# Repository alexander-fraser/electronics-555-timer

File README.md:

# electronics-555-timer-rev1-0
A single-board solution to the three operating modes of the 555 timer (astable, monostable, and bistable).

Jumpers to bridge for each operating mode:
Astable: 2,4,5;
Monostable: 1,3,4;
Bistable: 1

Issue Log:
- Add +/- markings to silkscreen at power input.
- In bistable mode, the chip resets when JP4 is touched.

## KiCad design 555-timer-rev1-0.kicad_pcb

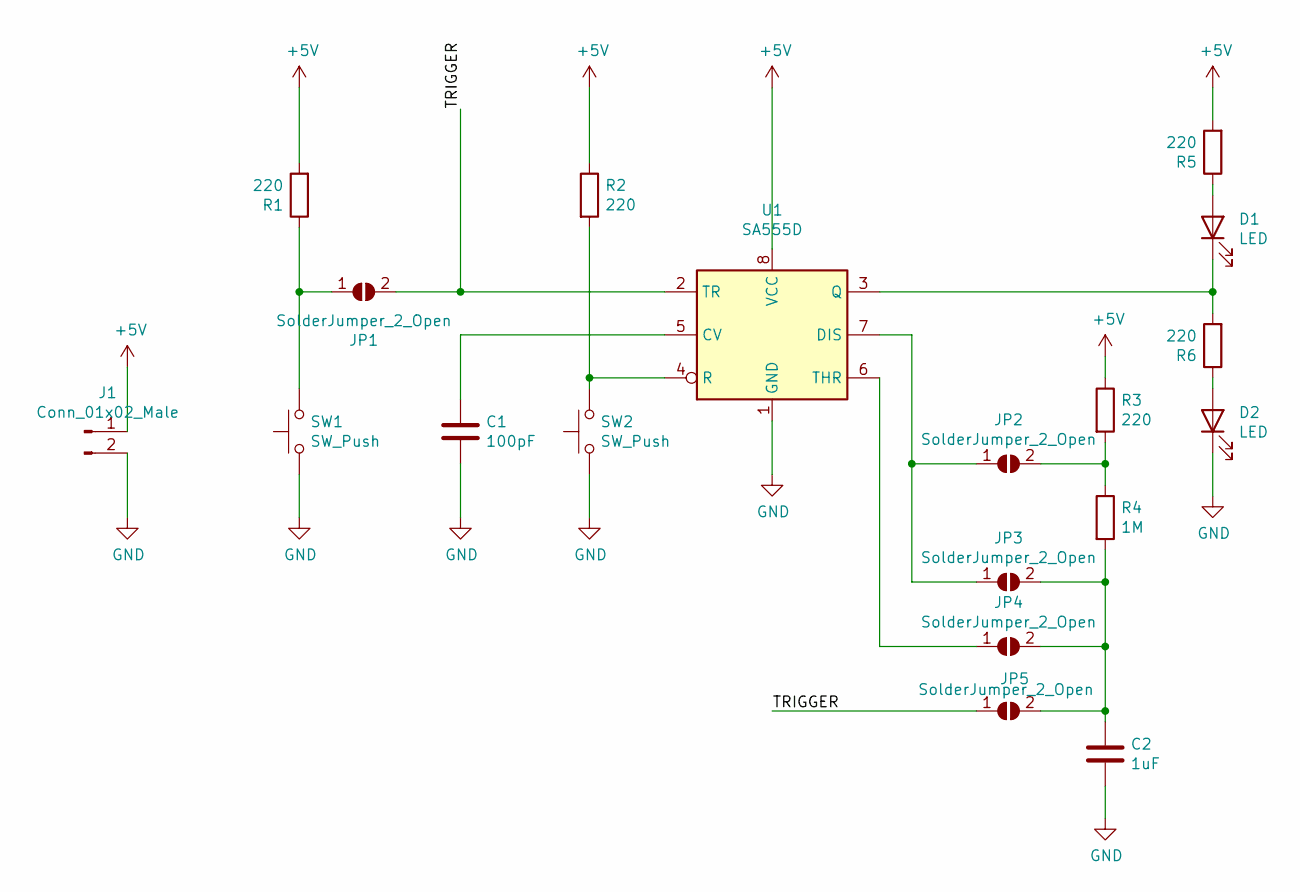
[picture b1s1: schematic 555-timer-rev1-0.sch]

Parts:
C1: 100pF; C_1206_3216Metric_Pad1.42x1.75mm_HandSolder
C2: 1uF; C_1206_3216Metric_Pad1.42x1.75mm_HandSolder
D1, D2: LED; LED_1206_3216Metric_Castellated
J1: Conn_01x02_Male; PinHeader_1x02_P2.54mm_Vertical
JP1, JP2, JP3, JP4, JP5: SolderJumper_2_Open; SolderJumper-2_P1.3mm_Open_TrianglePad1.0x1.5mm
R1, R2, R3, R5, R6: 220; R_1206_3216Metric_Pad1.42x1.75mm_HandSolder
R4: 1M; R_1206_3216Metric_Pad1.42x1.75mm_HandSolder
SW1, SW2: SW_Push; SW_SPST_PTS647
U1: SA555D; SOIC-8_3.9x4.9mm_P1.27mm

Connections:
+5V: J1.1, R1.2, R2.1, R3.1, R5.2, U1.8 (VCC)
/TRIGGER: JP1.2 (B), JP5.1 (A), U1.2 (TR)
GND: C1.2, C2.2, D2.1 (K), J1.2, SW1.1, SW2.1, U1.1 (GND)
unnamed: C1.1, U1.5 (CV)
unnamed: C2.1, JP3.2 (B), JP4.2 (B), JP5.2 (B), R4.2
unnamed: D1.1 (K), R6.2, U1.3 (Q)
unnamed: D1.2 (A), R5.1
unnamed: D2.2 (A), R6.1
unnamed: JP1.1 (A), R1.1, SW1.2
unnamed: JP2.1 (A), JP3.1 (A), U1.7 (DIS)
unnamed: JP2.2 (B), R3.2, R4.1
unnamed: JP4.1 (A), U1.6 (THR)
unnamed: R2.2, SW2.2, U1.4 (R)

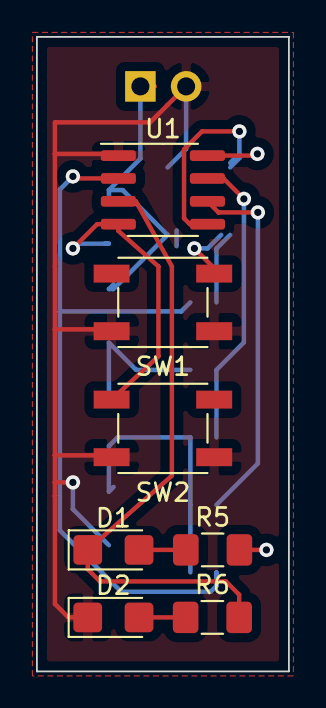
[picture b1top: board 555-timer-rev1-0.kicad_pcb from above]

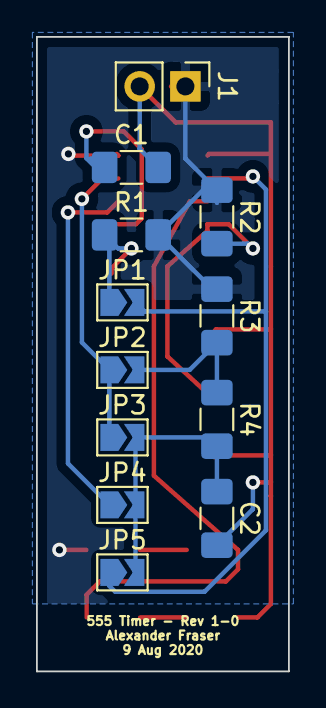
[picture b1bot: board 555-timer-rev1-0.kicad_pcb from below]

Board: 2 copper layers, 14.0 x 35.2 mm, 19 parts (12 on the bottom side), 13 nets.

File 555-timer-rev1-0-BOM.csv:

"Id";"Designator";"Package";"Quantity";"Designation";"Supplier and ref";
1;"U1";"SOIC-8_3.9x4.9mm_P1.27mm";1;"SA555D";;;
2;"SW2,SW1";"SW_SPST_PTS647";2;"SW_Push";;;
3;"R6,R5,R3,R2,R1";"R_1206_3216Metric_Pad1.42x1.75mm_HandSolder";5;"220";;;
4;"R4";"R_1206_3216Metric_Pad1.42x1.75mm_HandSolder";1;"1M";;;
5;"JP4,JP3,JP2,JP5,JP1";"SolderJumper-2_P1.3mm_Open_TrianglePad1.0x1.5mm";5;"SolderJumper_2_Open";;;
6;"J1";"PinHeader_1x02_P2.54mm_Vertical";1;"Conn_01x02_Male";;;
7;"D2,D1";"LED_1206_3216Metric_Castellated";2;"LED";;;
8;"C2";"C_1206_3216Metric_Pad1.42x1.75mm_HandSolder";1;"1uF";;;
9;"C1";"C_1206_3216Metric_Pad1.42x1.75mm_HandSolder";1;"100pF";;;

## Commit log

2020-08-03 Initial commit.
2020-08-03 Create schematic for astable mode.
2020-08-07 Add bistable reset switch to schematic.
2020-08-07 Add astable and bistable switches and jumpers.
2020-08-09 Create and assign layout for switches.
2020-08-09 Start laying out PCB.
2020-08-09 Update PCB layout for 2-layer board.
2020-08-09 Finish PCB layout.
2020-08-09 Add name to silkscreen.
2020-08-09 Reverse power rail orientation.
2020-08-10 Add VCC and GND fill zones.
2020-08-10 Add documentation for jumpers.
2020-08-15 Add plots and pictures of PCB.
2020-08-15 Move plots to a separate directory.
2020-08-15 Add pictures of PCB to README.
2020-08-15 Remove unnecessary files.
2020-09-06 Add images of previous versions.
2020-09-06 Add gerber plots.
2020-09-12 Update pictures.
2020-09-12 Add new pictures.
2020-09-12 Add outstanding issues.
